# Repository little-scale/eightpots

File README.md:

# eightpots
Minimal Controller with Eight Pots made with a Teensy LC

Contains Arduino code, Kicad schematics and PCB, generated Gerber and drill files, position and BOM files, and STL files for the casing.

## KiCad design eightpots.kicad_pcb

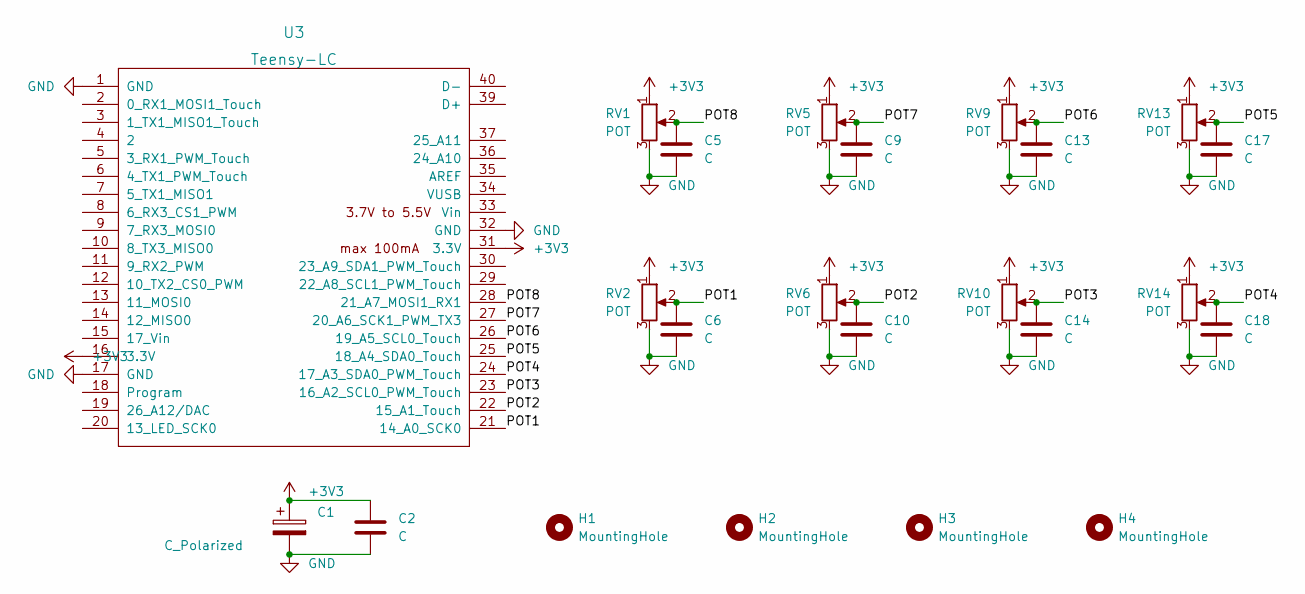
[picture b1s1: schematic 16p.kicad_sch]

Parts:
C1: C_Polarized; CAP_EEEFN1E100R
C2, C5, C6, C9, C10, C13, C14, C17, C18: C; C_0805_2012Metric_Pad1.18x1.45mm_HandSolder
H1, H2, H3, H4: MountingHole; MountingHole_3.2mm_M3
RV1, RV2, RV5, RV6, RV9, RV10, RV13, RV14: POT; Potentiometer_Alps_RK09K_Single_Vertical
U3: Teensy-LC; Teensy30_31_32_LC

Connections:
+3V3: C1.1, C2.1, RV1.1, RV2.1, RV5.1, RV6.1, RV9.1, RV10.1, RV13.1, RV14.1, U3.16 (3.3V), U3.31 (3.3V)
/POT1: C6.1, RV2.2, U3.21 (14_A0_SCK0)
/POT2: C10.1, RV6.2, U3.22 (15_A1_Touch)
/POT3: C14.1, RV10.2, U3.23 (16_A2_SCL0_PWM_Touch)
/POT4: C18.1, RV14.2, U3.24 (17_A3_SDA0_PWM_Touch)
/POT5: C17.1, RV13.2, U3.25 (18_A4_SDA0_Touch)
/POT6: C13.1, RV9.2, U3.26 (19_A5_SCL0_Touch)
/POT7: C9.1, RV5.2, U3.27 (20_A6_SCK1_PWM_TX3)
/POT8: C5.1, RV1.2, U3.28 (21_A7_MOSI1_RX1)
GND: C1.2, C2.2, C5.2, C6.2, C9.2, C10.2, C13.2, C14.2, C17.2, C18.2, RV1.3, RV1.MP, RV2.3, RV2.MP, RV5.3, RV5.MP, RV6.3, RV6.MP, RV9.3, RV9.MP, RV10.3, RV10.MP, RV13.3, RV13.MP, RV14.3, RV14.MP, U3.1 (GND), U3.17 (GND), U3.32 (GND)

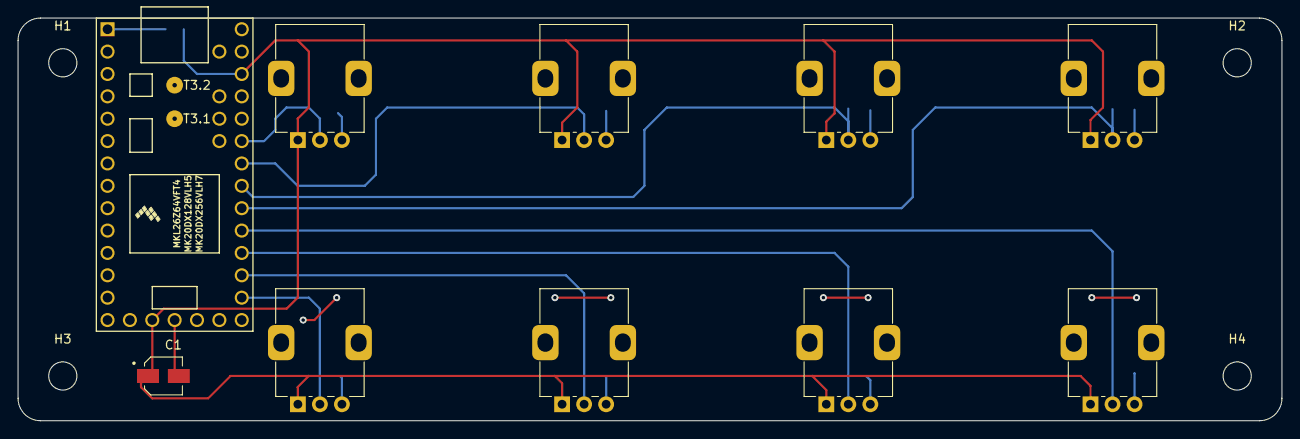
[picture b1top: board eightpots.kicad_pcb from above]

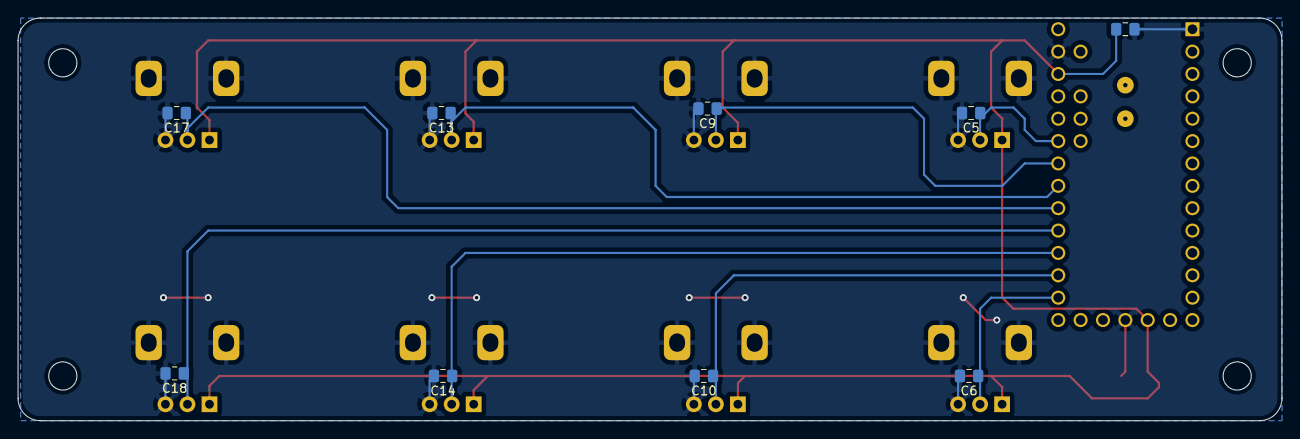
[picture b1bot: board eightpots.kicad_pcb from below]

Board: 2 copper layers, 143.5 x 45.7 mm, 23 parts (9 on the bottom side), 10 nets.
